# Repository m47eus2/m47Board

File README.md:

# m47Board

## Custom PCB designed for STM32 Dev Board
- STM32C031C6T6 MCU
- HSE and LSE external oscillators
- SWD programming interface
- Goldpin headers for all GPIO pins
- User button and user LED
- TLV1117LV33 5V to 3.3V 1A LDO
- RST button

## PCB render

## Schematic

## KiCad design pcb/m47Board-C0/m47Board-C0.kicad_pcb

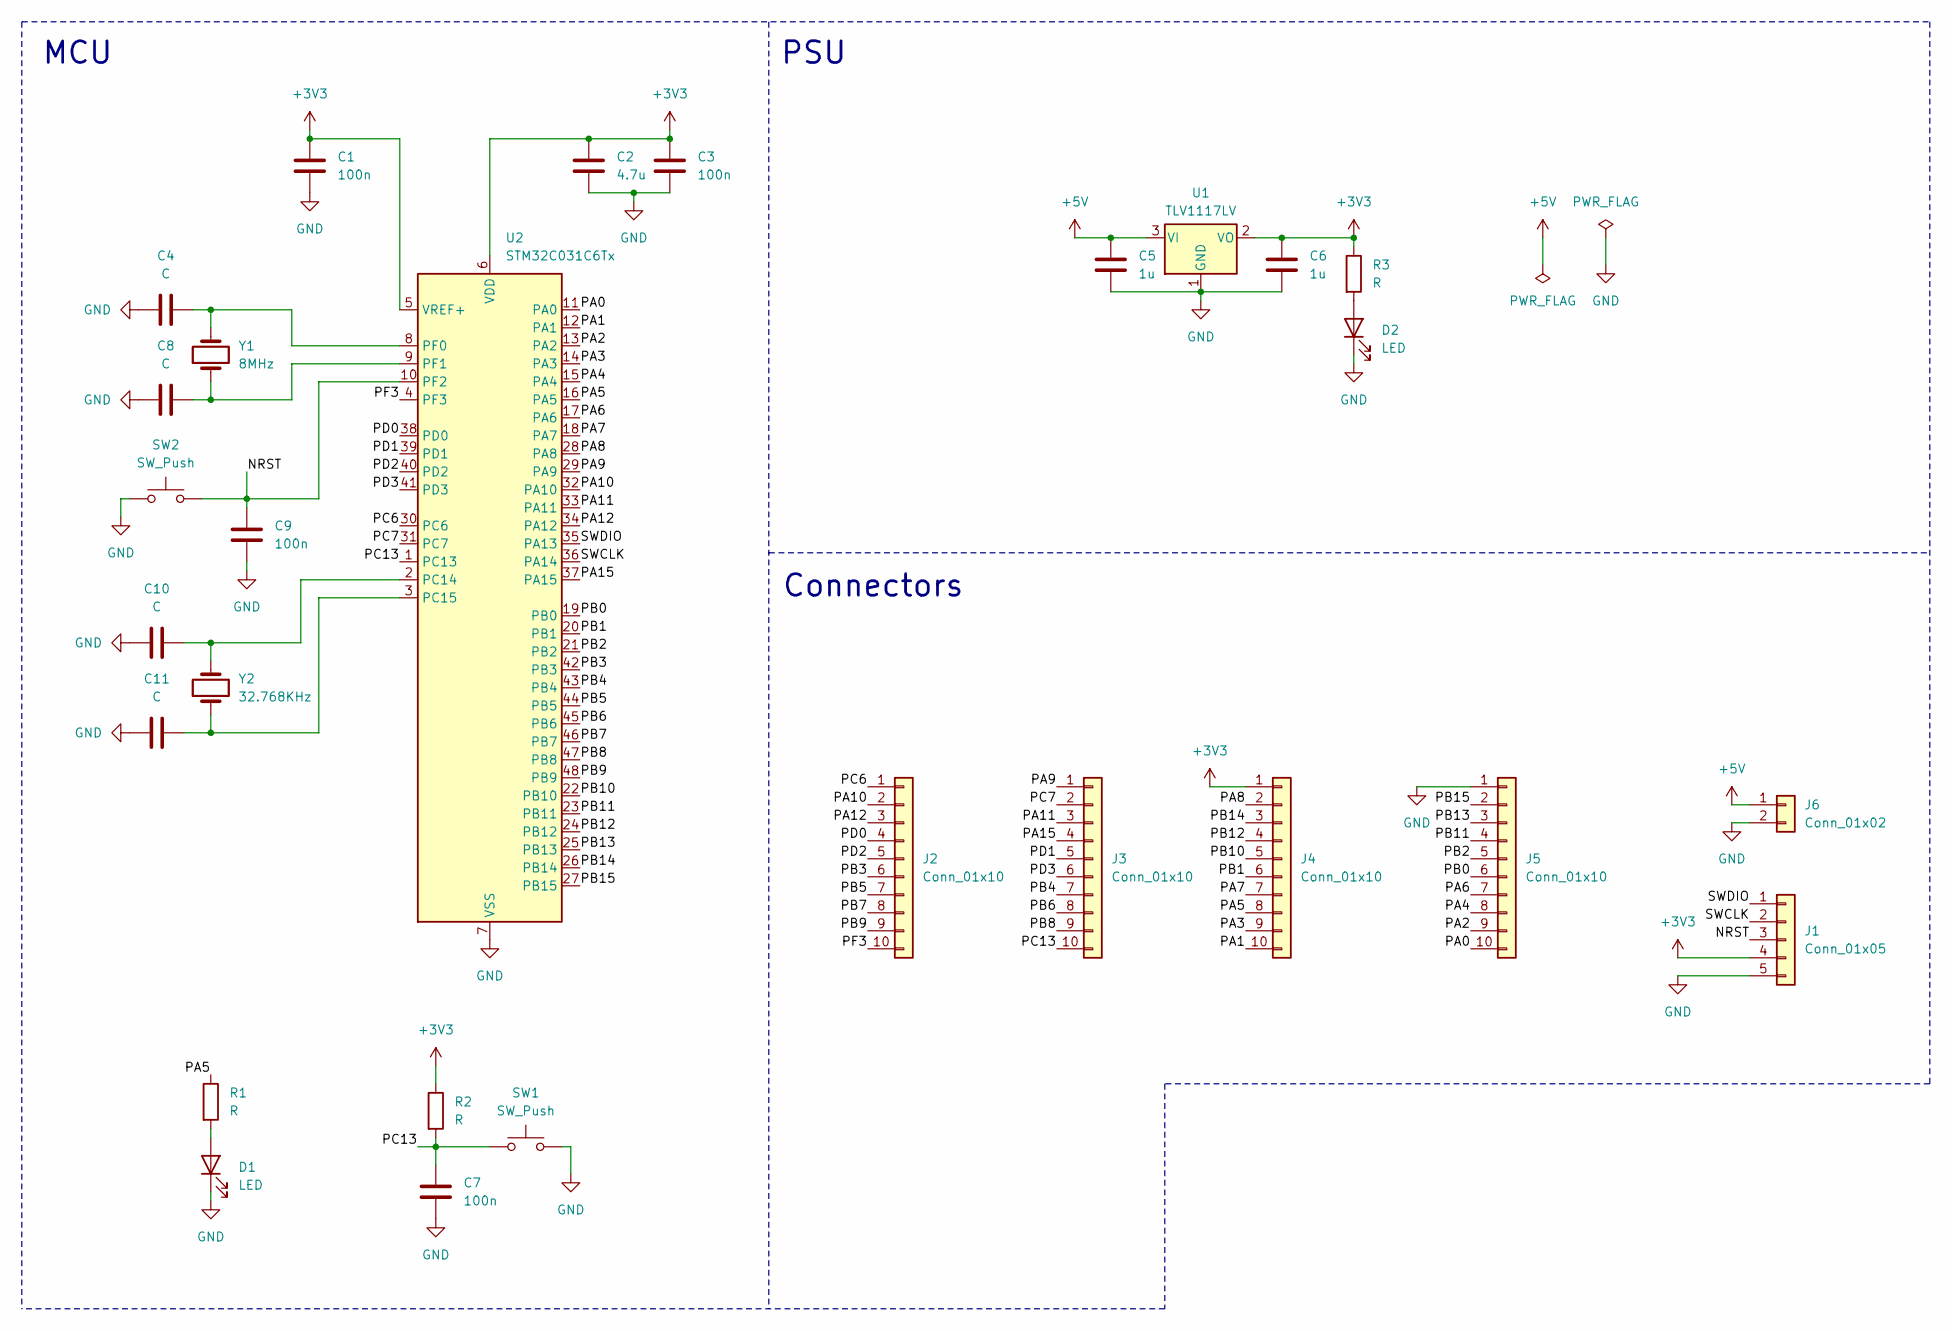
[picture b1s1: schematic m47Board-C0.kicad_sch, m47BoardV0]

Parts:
C1, C3, C7, C9: 100n; C_0805_2012Metric_Pad1.18x1.45mm_HandSolder
C2: 4.7u; C_0805_2012Metric_Pad1.18x1.45mm_HandSolder
C4, C8, C10, C11: C; C_0805_2012Metric_Pad1.18x1.45mm_HandSolder
C5, C6: 1u; C_0805_2012Metric_Pad1.18x1.45mm_HandSolder
D1, D2: LED; LED_0805_2012Metric_Pad1.15x1.40mm_HandSolder
J1: Conn_01x05; PinHeader_1x05_P2.54mm_Vertical
J2, J3, J4, J5: Conn_01x10; PinHeader_1x10_P2.54mm_Vertical
J6: Conn_01x02; PinHeader_1x02_P2.54mm_Vertical
R1, R2, R3: R; R_0805_2012Metric_Pad1.20x1.40mm_HandSolder
SW1, SW2: SW_Push; SW_Push_1P1T_NO_E-Switch_TL3301NxxxxxG
U1: TLV1117LV; SOT-223-LTV1117LV
U2: STM32C031C6Tx; LQFP-48_7x7mm_P0.5mm
Y1: 8MHz; Crystal_SMD_HC49-SD
Y2: 32.768KHz; Crystal_SMD_Abracon_ABS25-4Pin_8.0x3.8mm

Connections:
+3V3: C1.1, C2.1, C3.1, C6.1, J1.4, J4.1, R2.1, R3.1, U1.2 (VO), U2.5 (VREF+), U2.6 (VDD)
+5V: C5.1, J6.1, U1.3 (VI)
/NRST: C9.1, J1.3, SW2.2, U2.10 (PF2)
/PA0: J5.10, U2.11 (PA0)
/PA1: J4.10, U2.12 (PA1)
/PA2: J5.9, U2.13 (PA2)
/PA3: J4.9, U2.14 (PA3)
/PA4: J5.8, U2.15 (PA4)
/PA5: J4.8, R1.1, U2.16 (PA5)
/PA6: J5.7, U2.17 (PA6)
/PA7: J4.7, U2.18 (PA7)
/PA8: J4.2, U2.28 (PA8)
/PA9: J3.1, U2.29 (PA9)
/PA10: J2.2, U2.32 (PA10)
/PA11: J3.3, U2.33 (PA11)
/PA12: J2.3, U2.34 (PA12)
/PA15: J3.4, U2.37 (PA15)
/PB0: J5.6, U2.19 (PB0)
/PB1: J4.6, U2.20 (PB1)
/PB2: J5.5, U2.21 (PB2)
/PB3: J2.6, U2.42 (PB3)
/PB4: J3.7, U2.43 (PB4)
/PB5: J2.7, U2.44 (PB5)
/PB6: J3.8, U2.45 (PB6)
/PB7: J2.8, U2.46 (PB7)
/PB8: J3.9, U2.47 (PB8)
/PB9: J2.9, U2.48 (PB9)
/PB10: J4.5, U2.22 (PB10)
/PB11: J5.4, U2.23 (PB11)
/PB12: J4.4, U2.24 (PB12)
/PB13: J5.3, U2.25 (PB13)
/PB14: J4.3, U2.26 (PB14)
/PB15: J5.2, U2.27 (PB15)
/PC6: J2.1, U2.30 (PC6)
/PC7: J3.2, U2.31 (PC7)
/PC13: C7.1, J3.10, R2.2, SW1.1, U2.1 (PC13)
/PD0: J2.4, U2.38 (PD0)
/PD1: J3.5, U2.39 (PD1)
/PD2: J2.5, U2.40 (PD2)
/PD3: J3.6, U2.41 (PD3)
/PF3: J2.10, U2.4 (PF3)
/SWCLK: J1.2, U2.36 (PA14)
/SWDIO: J1.1, U2.35 (PA13)
GND: C1.2, C2.2, C3.2, C4.1, C5.2, C6.2, C7.2, C8.1, C9.2, C10.1, C11.1, D1.1 (K), D2.1 (K), J1.5, J5.1, J6.2, SW1.2, SW2.1, U1.1 (GND), U2.7 (VSS)
unnamed: D1.2 (A), R1.2
unnamed: D2.2 (A), R3.2
unnamed: C10.2, U2.2 (PC14), Y2.2
unnamed: C11.2, U2.3 (PC15), Y2.1
unnamed: C4.2, U2.8 (PF0), Y1.2
unnamed: C8.2, U2.9 (PF1), Y1.1

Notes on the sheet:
MCU
Connectors
PSU

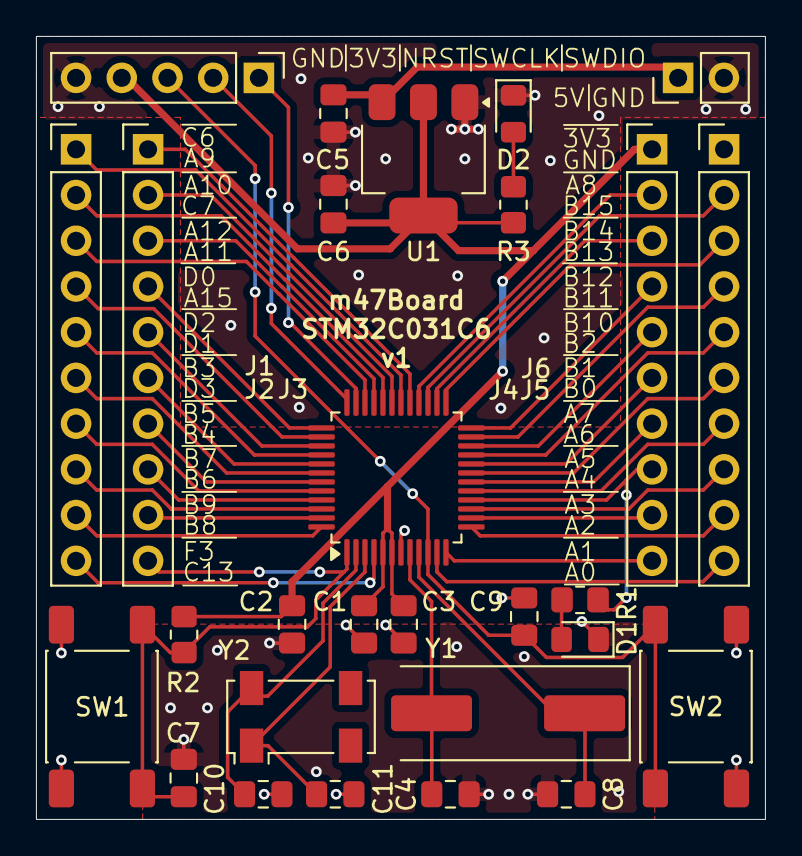
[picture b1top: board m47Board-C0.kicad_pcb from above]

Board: 2 copper layers, 40.5 x 43.5 mm, 28 parts (0 on the bottom side), 50 nets.

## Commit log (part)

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2026-04-07 Adding KiCad project files and docs dir
2026-04-28 Change project name
2026-04-28 Update gitignore
2026-04-28 Add R values
2026-04-28 Remove gerber files from m47Board-C0
2026-06-27 Returning to V0
2026-06-28 Part of schematic and pinout for m47Board-H503
2026-06-29 Update m47Board-H503 schematic
